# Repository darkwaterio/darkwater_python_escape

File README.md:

# escape
Library for the escape board

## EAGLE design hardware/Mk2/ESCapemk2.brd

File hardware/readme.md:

Placeholder for the Escape board hardware files

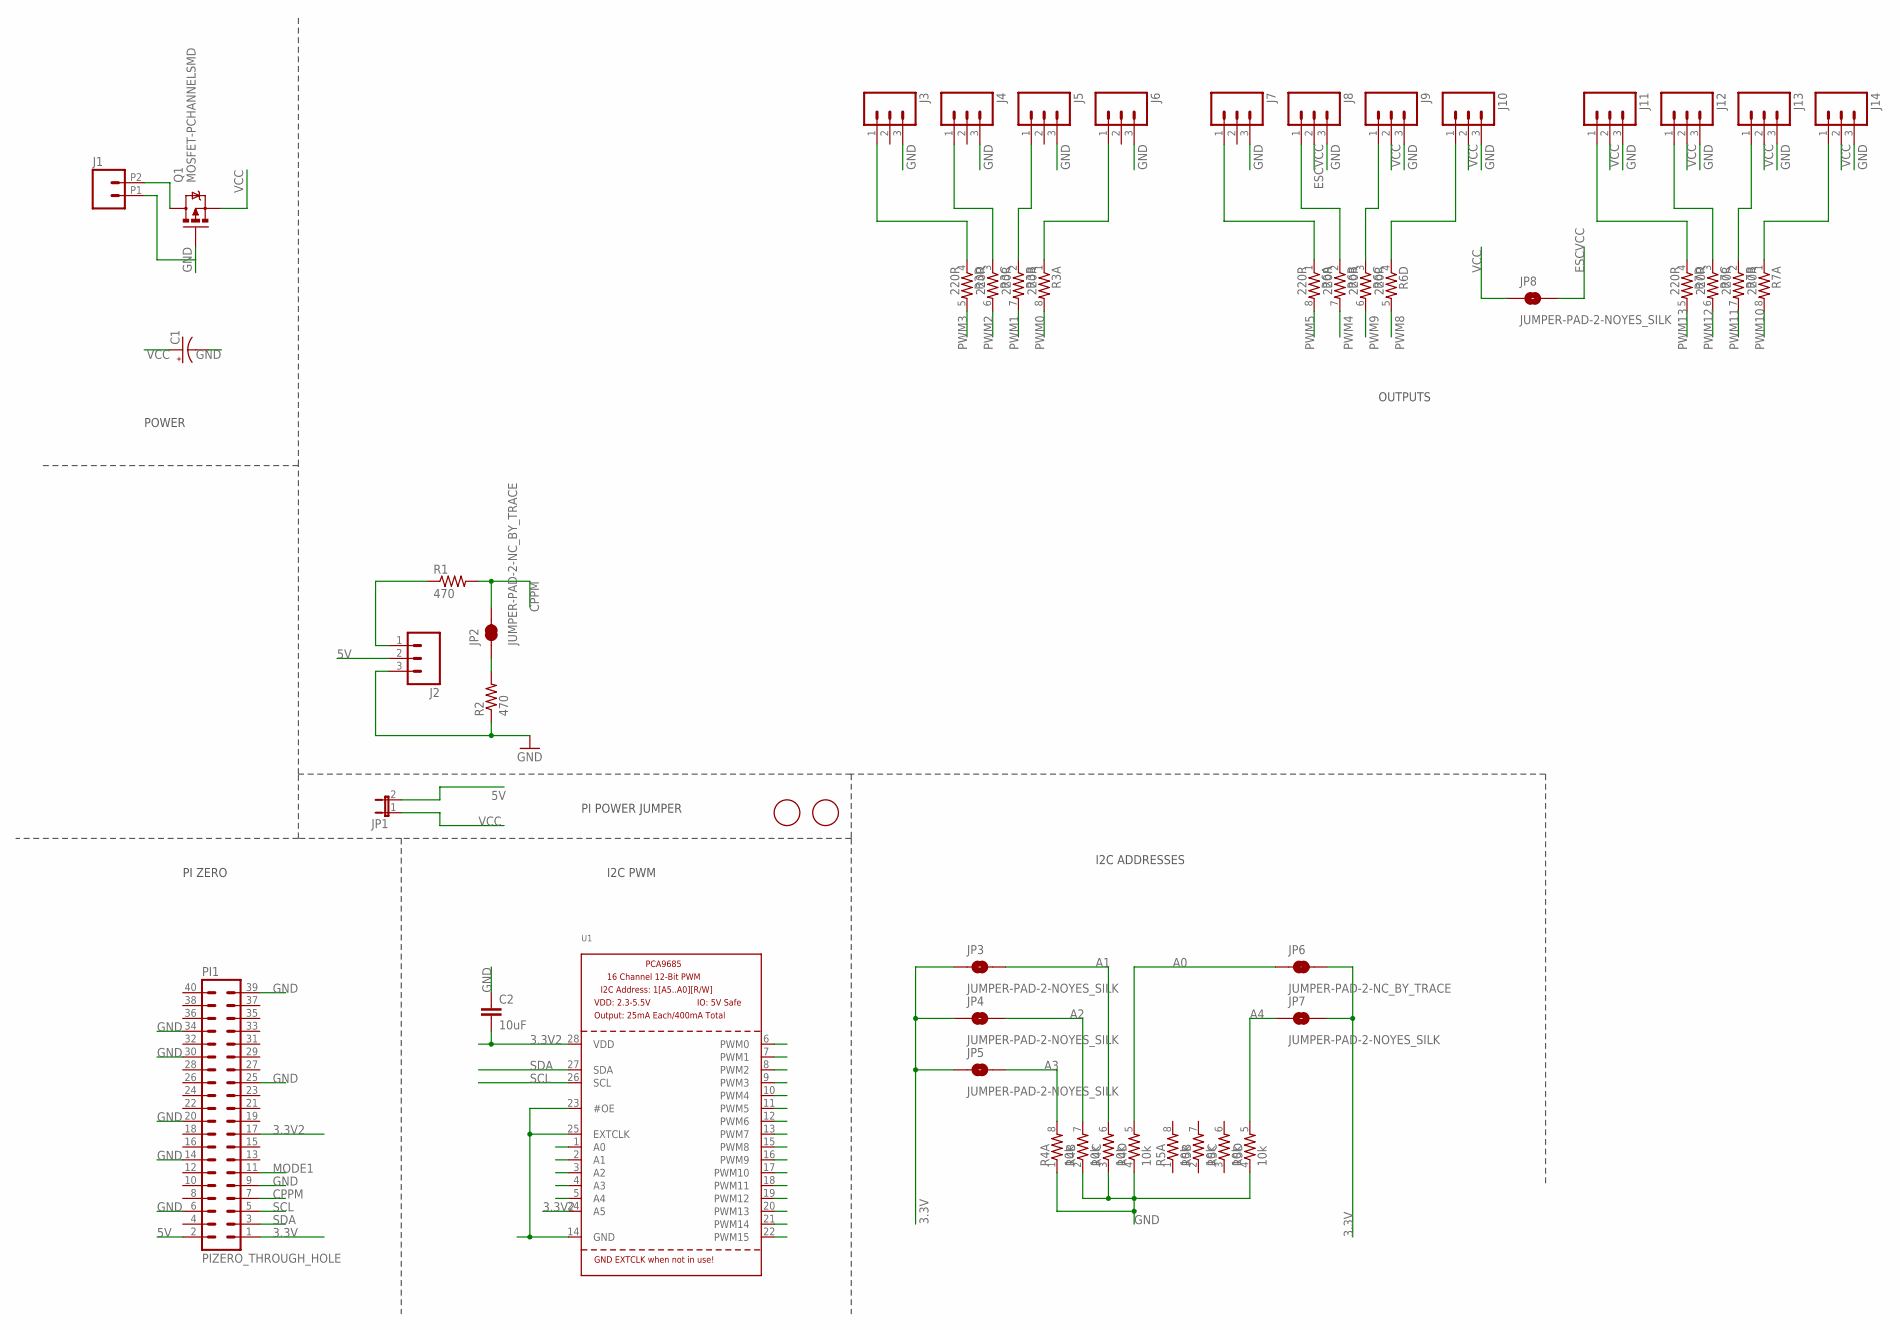
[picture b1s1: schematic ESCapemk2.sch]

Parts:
C1: CAP_POLPTH1; CPOL-RADIAL-100UF-25V
C2: 10uF; 0805
FID1, FID2: FIDUCIAL; FIDUCIAL_1MM
J1: M022.54MM_SCREWTERM; 1X02_2.54_SCREWTERM
J2, J3, J4, J5, J6, J7, J8, J9, J10, J11, J12, J13, J14: M03LOCK; 1X03_LOCK
JP1: JUMPER-2PTH_LOCK; 1X02_LOCK
JP2, JP6: JUMPER-PAD-2-NC_BY_TRACE; PAD-JUMPER-2-NC_BY_TRACE_YES_SILK
JP3, JP4, JP5, JP7, JP8: JUMPER-PAD-2-NOYES_SILK; PAD-JUMPER-2-NO_YES_SILK
PI1: PIZERO_THROUGH_HOLE; PIZERO_THOUGH_HOLE
Q1: MOSFET-PCHANNELSMD; SOT23-3
R1, R2: 470; 0805
R3, R6, R7: 220R; 0603-ARV
R4, R5: 10k; 0603-ARV
U1: PCA9685; TSSOP28

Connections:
3.3V: JP3.1, JP4.1, JP5.1, JP6.2, JP7.2, PI1.1
3.3V2: C2.2, PI1.17, U1.24 (A5), U1.28 (VDD)
5V: J2.2, JP1.2, PI1.2
A0: JP6.1, R4.5 (2), U1.1 (A0)
A1: JP3.2, R4.6 (2), U1.2 (A1)
A2: JP4.2, R4.7 (2), U1.3 (A2)
A3: JP5.2, R4.8 (2), U1.4 (A3)
A4: JP7.1, R5.5 (2), U1.5 (A4)
CPPM: JP2.2, PI1.7, R1.2
ESCVCC: J8.2, JP8.2
GND: C1.2 (-), C2.1, J1.P1 (1), J2.3, J3.3, J4.3, J5.3, J6.3, J7.3, J8.3, J9.3, J10.3, J11.3, J12.3, J13.3, J14.3, PI1.6, PI1.9, PI1.14, PI1.20, PI1.25, PI1.30, PI1.34, PI1.39, Q1.1 (G), R2.1, R4.1, R4.2 (1), R4.3 (1), R4.4 (1), R5.4 (1), U1.14 (GND), U1.23 (#OE), U1.25 (EXTCLK)
MODE1: PI1.11
unnamed: J3.1, R3.4 (1)
unnamed: J4.1, R3.3 (1)
unnamed: J6.1, R3.1
unnamed: J5.1, R3.2 (1)
unnamed: J7.1, R6.1
unnamed: J8.1, R6.2 (1)
unnamed: J10.1, R6.4 (1)
unnamed: J9.1, R6.3 (1)
unnamed: J11.1, R7.4 (1)
unnamed: J12.1, R7.3 (1)
unnamed: J14.1, R7.1
unnamed: J13.1, R7.2 (1)
unnamed: J2.1, R1.1
unnamed: JP2.1, R2.2
unnamed: J1.P2 (2), Q1.3 (D)
PWM0: R3.8 (2), U1.6 (PWM0)
PWM1: R3.7 (2), U1.7 (PWM1)
PWM2: R3.6 (2), U1.8 (PWM2)
PWM3: R3.5 (2), U1.9 (PWM3)
PWM4: R6.7 (2), U1.10 (PWM4)
PWM5: R6.8 (2), U1.11 (PWM5)
PWM6: U1.12 (PWM6)
PWM7: U1.13 (PWM7)
PWM8: R6.5 (2), U1.15 (PWM8)
PWM9: R6.6 (2), U1.16 (PWM9)
PWM10: R7.8 (2), U1.17 (PWM10)
PWM11: R7.7 (2), U1.18 (PWM11)
PWM12: R7.6 (2), U1.19 (PWM12)
PWM13: R7.5 (2), U1.20 (PWM13)
PWM14: U1.21 (PWM14)
PWM15: U1.22 (PWM15)
SCL: PI1.5, U1.26 (SCL)
SDA: PI1.3, U1.27 (SDA)
VCC: C1.1 (+), J9.2, J10.2, J11.2, J12.2, J13.2, J14.2, JP1.1, JP8.1, Q1.2 (S)

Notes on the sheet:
I2C ADDRESSES
PI ZERO
I2C PWM
POWER
OUTPUTS
PI POWER JUMPER

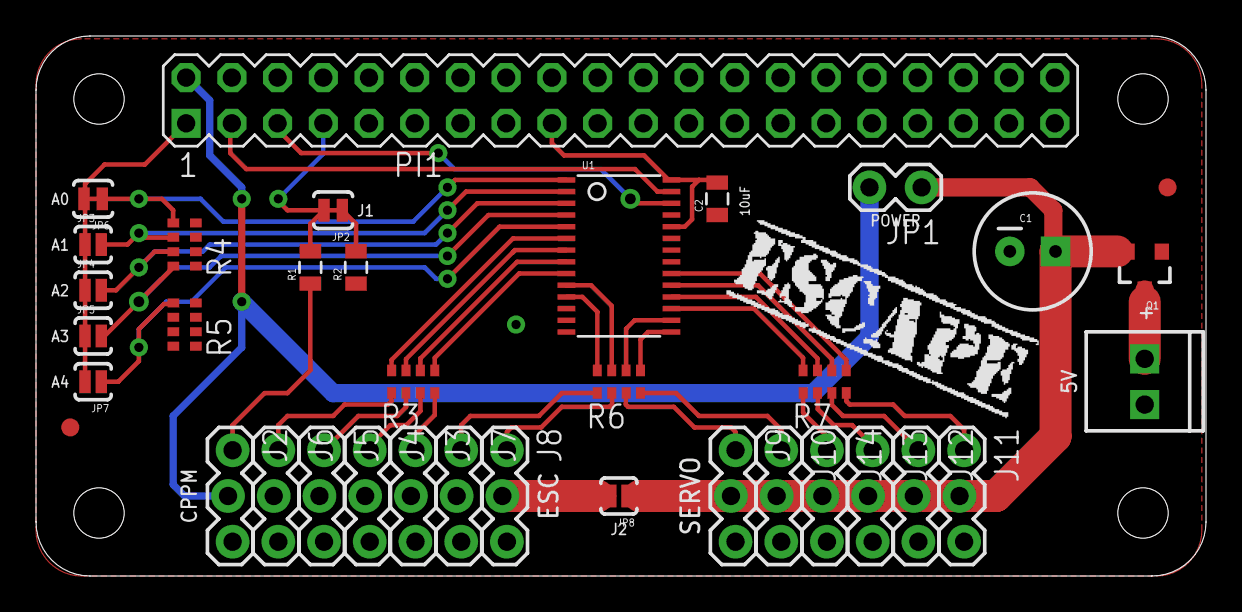
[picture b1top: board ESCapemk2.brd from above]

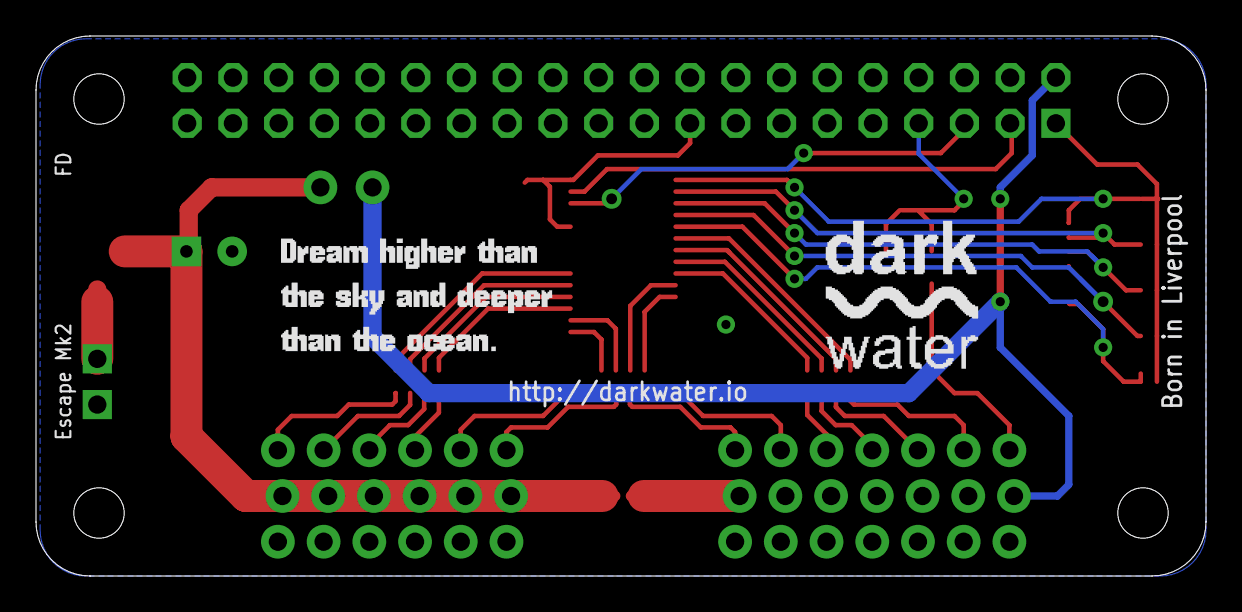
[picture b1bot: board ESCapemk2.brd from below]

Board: 2 copper layers, 65.0 x 30.0 mm, 39 parts (2 on the bottom side), 41 nets.

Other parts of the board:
U$4: DREAM
U$5: DARKWATER
U$6: ESCAPENEW

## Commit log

2016-03-31 Initial test code
2016-03-31 test
2016-03-31 Quick test fixes
2016-04-02 Updating library
2016-04-02 updated for angle test
2016-04-02 quick example update for now
2016-04-03 debugging
2016-04-03 Added correction factor
2016-04-03 Added correction factor for PCA chip frequency
2016-04-03 Added min and max frequency settings
2016-04-03 Added indentation
2016-04-30 Change structure
2016-04-30 change structre
2016-07-02 Added hardware directory
2016-07-08 Mk2 hardware files
2016-07-08 added CC
2016-08-13 Big update
    Needs testing
2016-08-15 moved example code
2016-08-15 new test files
2016-08-15 Updated class
2016-08-15 motor test
2016-08-15 library change
2016-08-15 oops
2016-08-15 test math
2016-08-15 debug
2016-08-15 new off
2016-08-15 escape update
2016-08-15 servo test code
2016-08-25 changed pins for new board test
2016-09-12 Updated smbus
2016-09-12 changed pins around for new board
2016-09-29 initial imu
2016-09-29 imu test
2016-09-29 print statement changed
2016-10-01 Changed motor speed to use ESC values
2016-10-04 created distribution
2016-10-04 fix limit bug in motor code
2016-10-04 updated dist

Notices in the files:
parts and their libraries:
SparkFun-Connectors: Licensing: Creative Commons ShareAlike 4.0 International - https://creativecommons.org/licenses/by-sa/4.0
